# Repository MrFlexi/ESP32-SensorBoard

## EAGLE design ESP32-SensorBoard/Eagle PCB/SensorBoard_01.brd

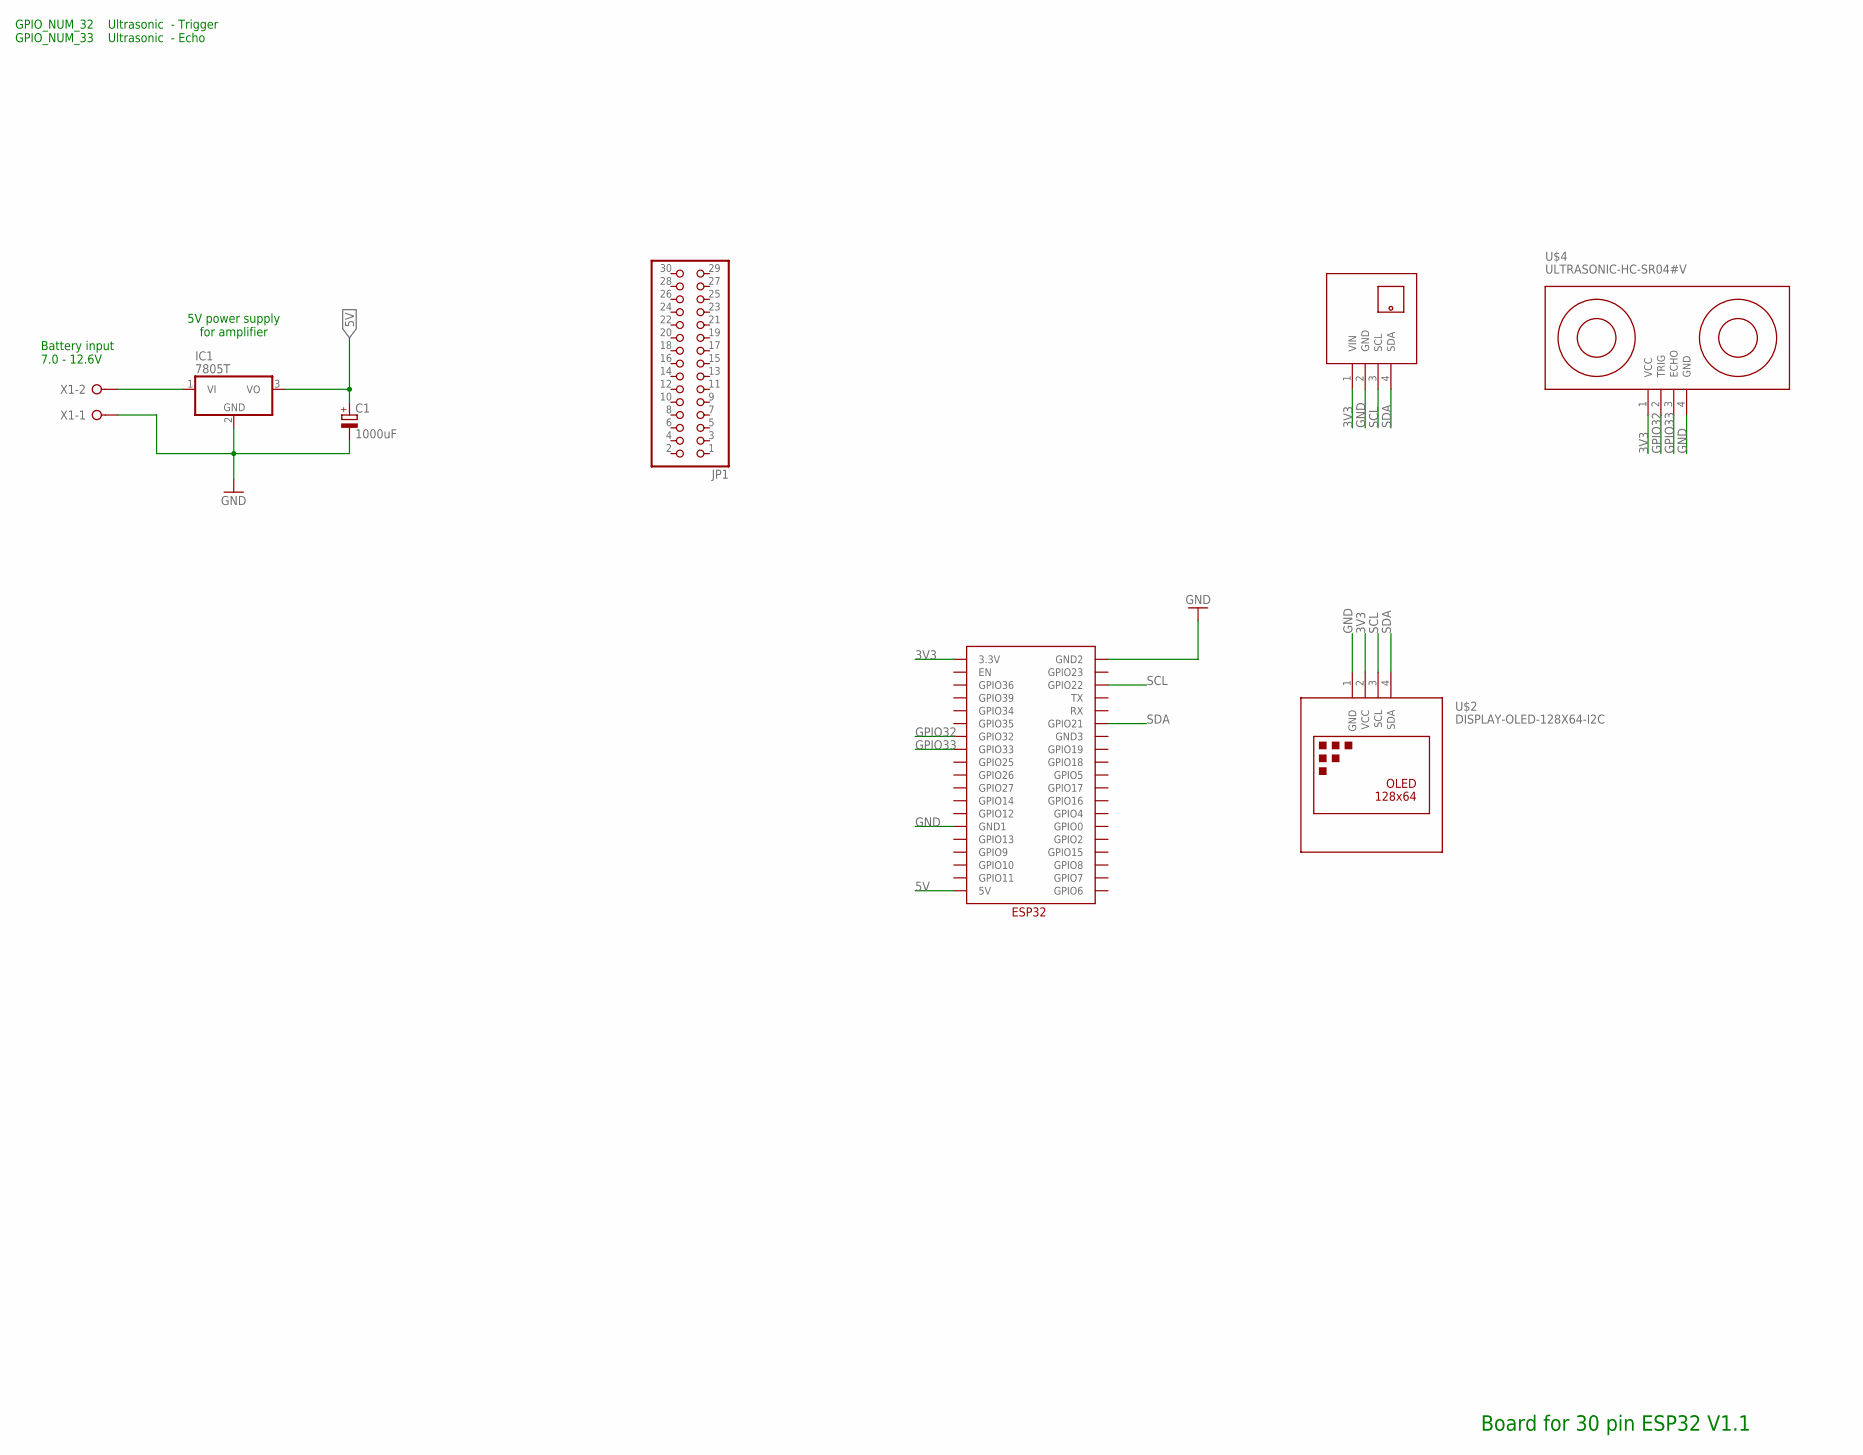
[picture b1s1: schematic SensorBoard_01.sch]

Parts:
C1: 1000uF; E5-10,5
IC1: 7805T; TO220H
JP1: PINHD-2X15; 2X15
U$1: ESP32
U$2: DISPLAY-OLED-128X64-I2C
U$3: TEMP-HUM-PRES-BME280
U$4: ULTRASONIC-HC-SR04#V
X1: W237-02P; W237-132

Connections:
3V3: U$1.3.3V, U$2.2 (VCC), U$3.1 (VIN), U$4.1 (VCC)
5V: C1.+, IC1.3 (VO), U$1.5V
BAT+: IC1.1 (VI), X1.2
GND: C1.-, IC1.2 (GND), U$1.GND1, U$1.GND2, U$2.1 (GND), U$3.2 (GND), U$4.4 (GND), X1.1
GPIO32: U$1.GPIO32, U$4.2 (TRIG)
GPIO33: U$1.GPIO33, U$4.3 (ECHO)
SCL: U$1.GPIO22, U$2.3 (SCL), U$3.3 (SCL)
SDA: U$1.GPIO21, U$2.4 (SDA), U$3.4 (SDA)

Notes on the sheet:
5V power supply for amplifier
Battery input 7.0 - 12.6V
Board for 30 pin ESP32 V1.1
GPIO_NUM_32 Ultrasonic - Trigger GPIO_NUM_33 Ultrasonic - Echo

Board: 2 copper layers, 8 parts (0 on the bottom side), 8 nets, no tracks yet.

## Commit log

2020-05-27 Init
2020-05-27 News
2020-05-27 lets try this
2020-05-27 Time Client
2020-05-27 Jsutils moved to LIB
2020-05-28 so ist es
2020-05-29 OTA Update
2020-05-29 Time info included
2020-05-30 Panel moves
2020-05-30 Display
2020-05-30 Display changed to oled
2020-05-31 Motor included
2020-06-02 Motor Library using build in mcpwm
2020-10-07 New things
2020-10-08 jaja
2022-12-15 PWM Fan included
2023-01-25 New init

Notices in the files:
parts and their libraries:
diy-modules: Released under the Creative Commons Attribution 4.0 International License: http://creativecommons.org/licenses/by/4.0
